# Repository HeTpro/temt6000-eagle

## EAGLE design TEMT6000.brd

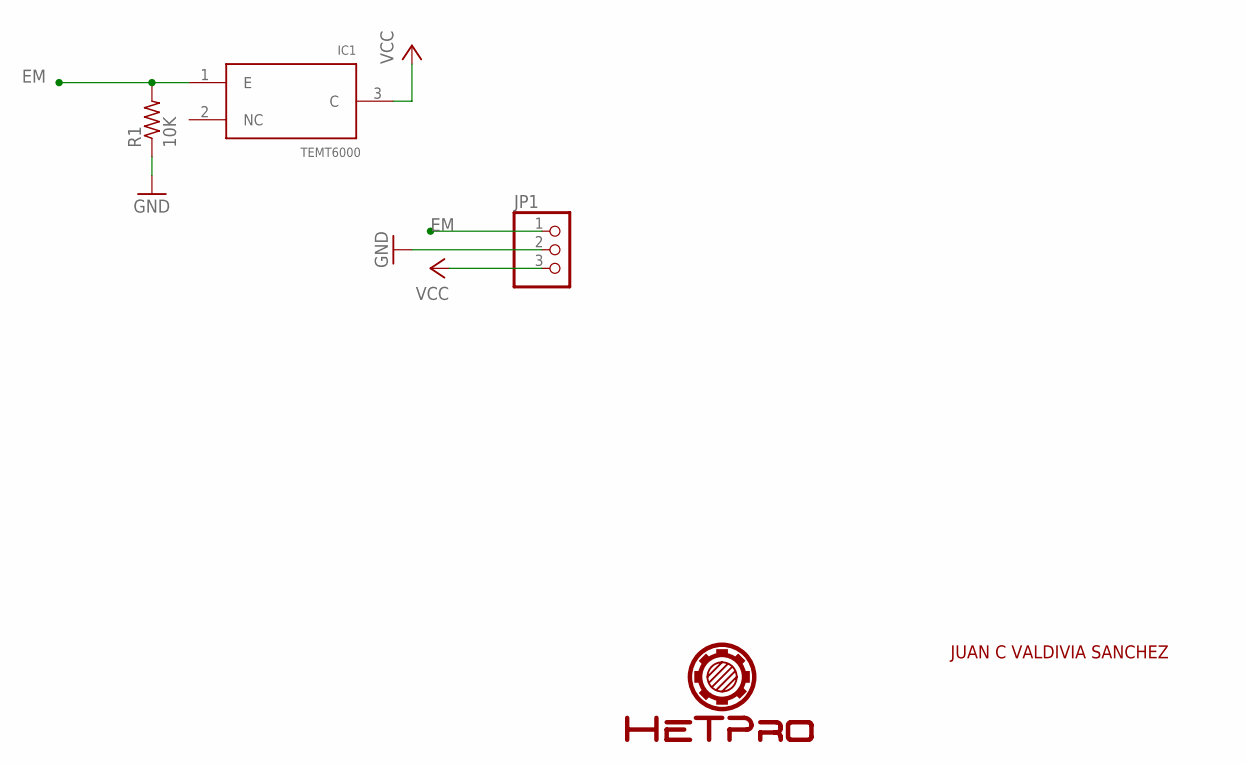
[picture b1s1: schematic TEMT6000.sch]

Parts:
IC1: TEMT6000
JP1: PINHD-1X3; 1X03
R1: 10K; R0603

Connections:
EM: IC1.1 (E), JP1.1, R1.2
GND: JP1.2, R1.1
VCC: IC1.3 (C), JP1.3

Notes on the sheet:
JUAN C VALDIVIA SANCHEZ

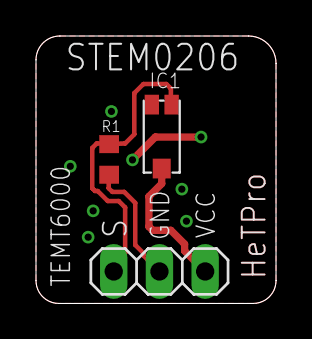
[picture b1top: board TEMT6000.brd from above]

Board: 2 copper layers, 13.3 x 14.9 mm, 3 parts (0 on the bottom side), 3 nets.

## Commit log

2015-04-22 :neckbeard: Added .gitattributes & .gitignore files
2015-04-22 Archivos
